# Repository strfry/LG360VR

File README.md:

# Summary

This about making the LG 360 VR Goggles usable with a normal DisplayPort outlet.

The LG360VR uses the "DisplayPort over USB-C" standard.
Our assumption is, that with little hardware effort, we can send a DisplayPort signal into it.

# Current State of things

- A passive PCB Adapter has been manufactured, though it doesn't work
- ~~Currently in the process of analyzing USB-PD communication, to figure out if this is the problem~~
  - Resolution: USB-PD Handshake is definitely necessary to get a display connection
- Now designing a new PCB with STM32F072 for PD Handshake and DisplayPort Redriver IC

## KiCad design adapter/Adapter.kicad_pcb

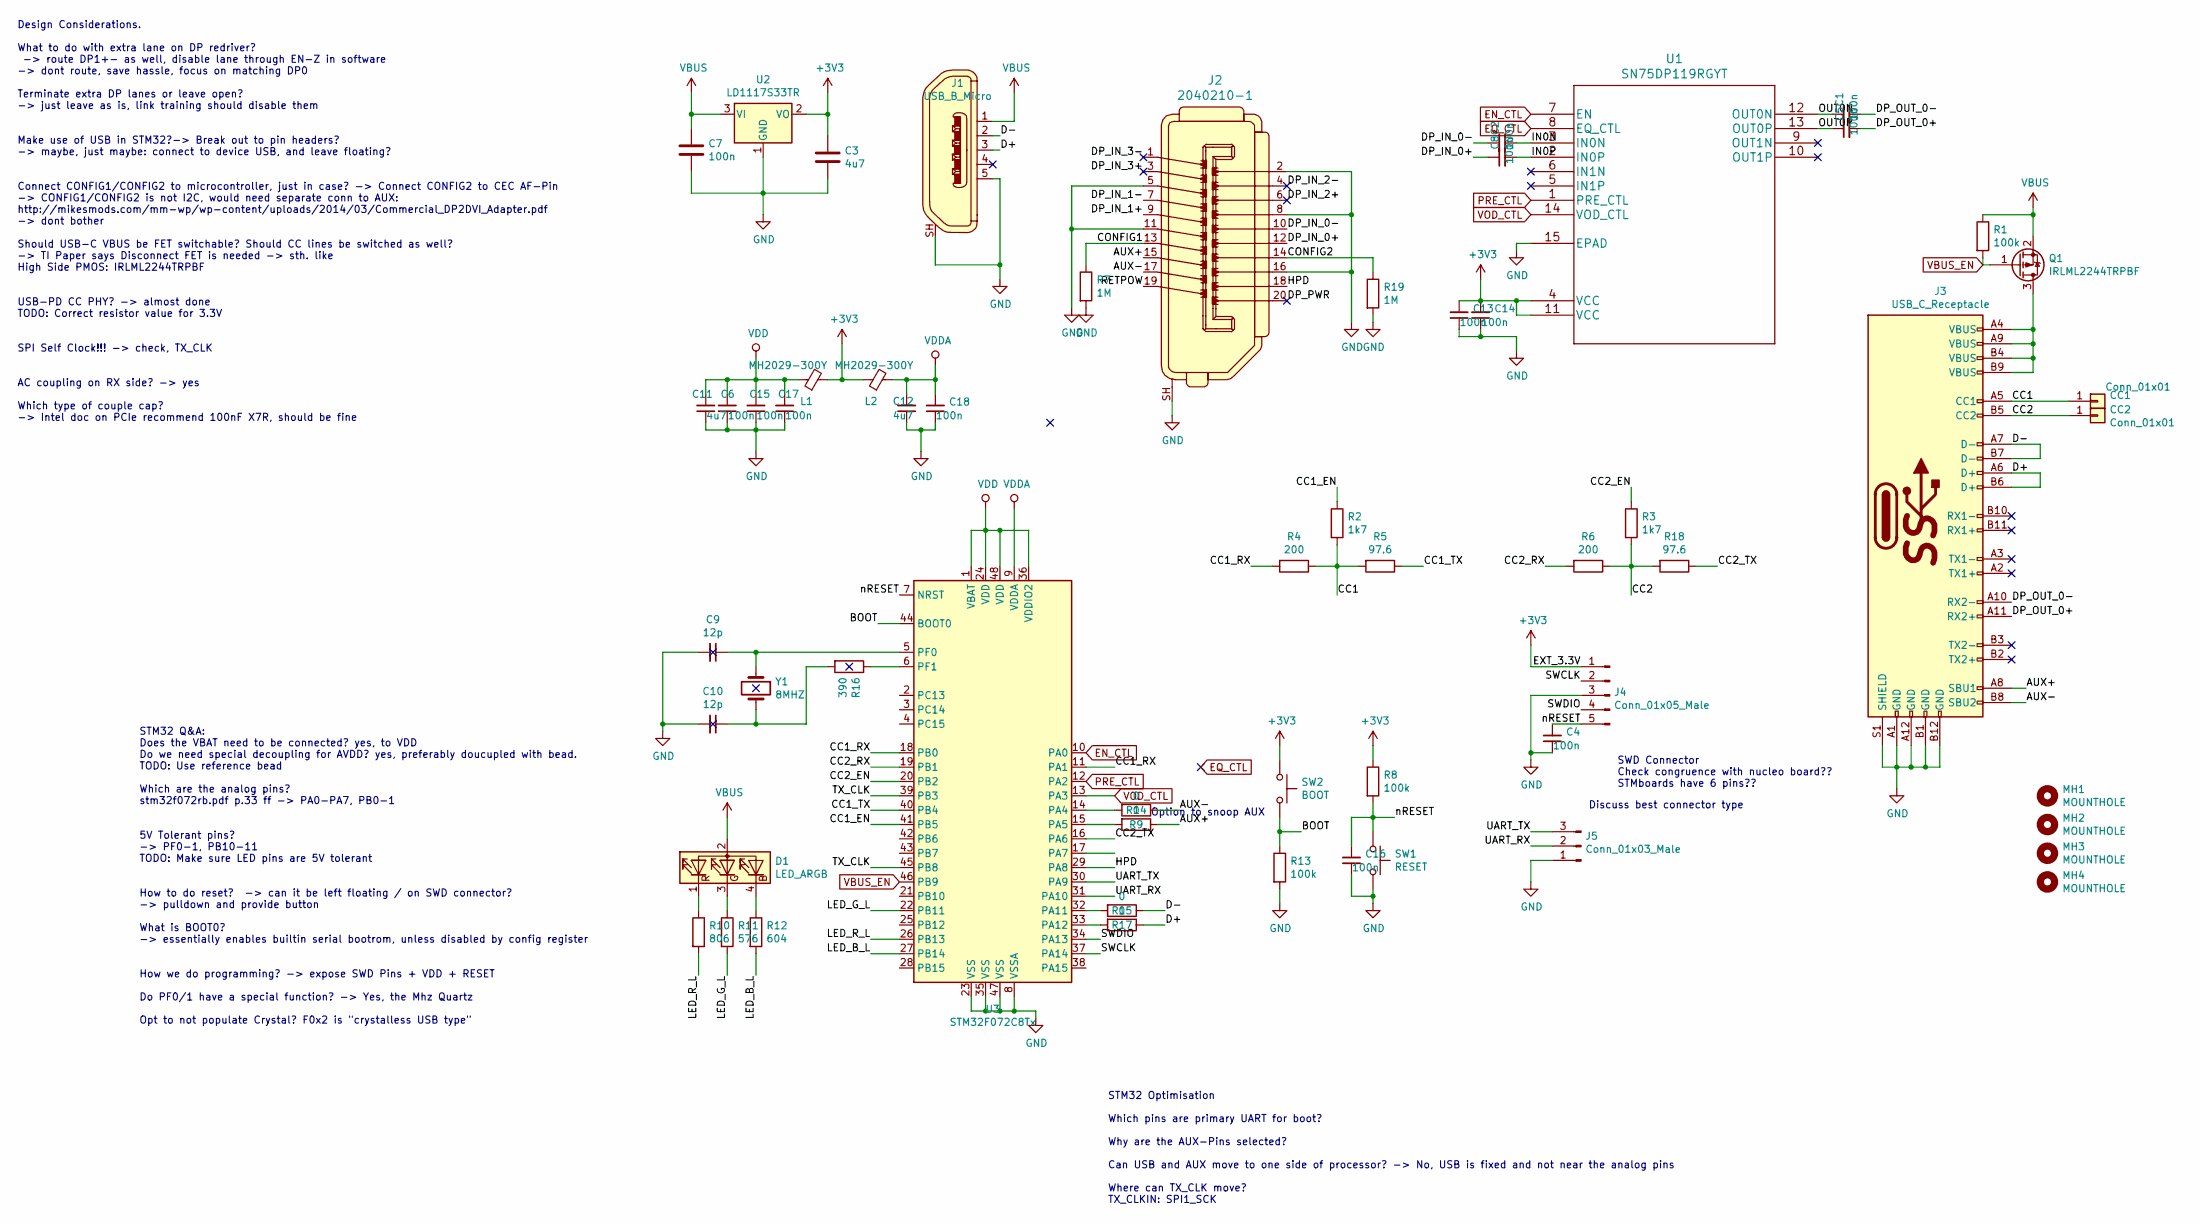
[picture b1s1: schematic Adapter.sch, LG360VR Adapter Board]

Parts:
C1, C2, C5, C8: 100n; C_0402_1005Metric
C3, C11, C12: 4u7; C_0603_1608Metric_Pad1.05x0.95mm_HandSolder
C4, C6, C7, C13, C14, C15, C16, C17, C18: 100n; C_0603_1608Metric_Pad1.05x0.95mm_HandSolder
C9, C10: 12p; C_0603_1608Metric_Pad1.05x0.95mm_HandSolder
CC1, CC2: Conn_01x01; TestPoint_Pad_D1.0mm
D1: LED_ARGB; LED_Cree-PLCC4_3.2x2.8mm_CCW
J1: USB_B_Micro; CONN-10118194-0001LF-FCI
J2: 2040210-1; DP1RD20JQ1R400
J3: USB_C_Receptacle; USB_C_Receptacle_Amphenol_12401610E4-2A
J4: Conn_01x05_Male; PinHeader_1x05_P2.54mm_Horizontal
J5: Conn_01x03_Male; PinHeader_1x03_P2.54mm_Horizontal
L1, L2: MH2029-300Y; L_0805_2012Metric_Pad1.15x1.40mm_HandSolder
MH1, MH2, MH3, MH4: MOUNTHOLE; MountingHole_2.5mm
Q1: IRLML2244TRPBF; SOT-23
R1, R8, R13: 100k; R_0603_1608Metric_Pad1.05x0.95mm_HandSolder
R2, R3: 1k7; R_0603_1608Metric_Pad1.05x0.95mm_HandSolder
R4, R6: 200; R_0603_1608Metric_Pad1.05x0.95mm_HandSolder
R5, R18: 97.6; R_0603_1608Metric_Pad1.05x0.95mm_HandSolder
R7, R19: 1M; R_0603_1608Metric_Pad1.05x0.95mm_HandSolder
R9, R14, R15, R17: 0; R_0603_1608Metric_Pad1.05x0.95mm_HandSolder
R10: 806; R_0603_1608Metric_Pad1.05x0.95mm_HandSolder
R11: 576; R_0603_1608Metric_Pad1.05x0.95mm_HandSolder
R12: 604; R_0603_1608Metric_Pad1.05x0.95mm_HandSolder
R16: 390; R_0603_1608Metric_Pad1.05x0.95mm_HandSolder
SW1: RESET; EVQPLMA15
SW2: BOOT; EVQPLMA15
U1: SN75DP119RGYT
U2: LD1117S33TR; SOT-223-3_TabPin2
U3: STM32F072C8Tx; LQFP-48_7x7mm_P0.5mm
Y1: 8MHZ; Crystal_SMD_TXC_7A-2Pin_5x3.2mm

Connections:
+3V3: C3.1, C13.2, C14.2, J4.1, L1.2, L2.1, R8.1, SW2.1, U1.4 (VCC), U1.11 (VCC), U2.2 (VO)
/AUX+: J2.15, J3.A8 (SBU1), R9.1
/AUX-: J2.17, J3.B8 (SBU2), R14.1
/BOOT: R13.1, SW2.2, U3.44 (BOOT0)
/CC1: CC1.1, J3.A5 (CC1), R2.2, R4.1, R5.2
/CC1_EN: R2.1, U3.41 (PB5)
/CC1_RX: R4.2, U3.11 (PA1), U3.18 (PB0)
/CC1_TX: R5.1, U3.40 (PB4)
/CC2: CC2.1, J3.B5 (CC2), R3.2, R6.1, R18.2
/CC2_EN: R3.1, U3.20 (PB2)
/CC2_RX: R6.2, U3.19 (PB1)
/CC2_TX: R18.1, U3.16 (PA6)
/CONFIG1: J2.13, R7.1
/CONFIG2: J2.14, R19.1
/D+: J1.3, J3.A6 (D+), J3.B6 (D+), R17.1
/D-: J1.2, J3.A7 (D-), J3.B7 (D-), R15.1
/DP_IN_0+: C8.1, J2.12
/DP_IN_0-: C2.1, J2.10
/DP_IN_1+: J2.9
/DP_IN_1-: J2.7
/DP_IN_2+: J2.6
/DP_IN_2-: J2.4
/DP_IN_3+: J2.3
/DP_IN_3-: J2.1
/DP_OUT_0+: C5.2, J3.A11 (RX2+)
/DP_OUT_0-: C1.2, J3.A10 (RX2-)
/DP_PWR: J2.20
/HPD: J2.18, U3.29 (PA8)
/IN0N: C2.2, U1.3 (IN0N)
/IN0P: C8.2, U1.2 (IN0P)
/LED_B_L: R12.2, U3.27 (PB14)
/LED_G_L: R11.2, U3.22 (PB11)
/LED_R_L: R10.2, U3.26 (PB13)
/OUT0N: C1.1, U1.12 (OUT0N)
/OUT0P: C5.1, U1.13 (OUT0P)
/RETPOW: J2.19
/SWCLK: J4.2, U3.37 (PA14)
/SWDIO: J4.4, U3.34 (PA13)
/TX_CLK: U3.39 (PB3), U3.45 (PB8)
/UART_RX: J5.2, U3.31 (PA10)
/UART_TX: J5.3, U3.30 (PA9)
/nRESET: C4.2, C16.2, J4.5, R8.2, SW1.1, U3.7 (NRST)
EN_CTL: U1.7 (EN), U3.10 (PA0)
EQ_CTL: U1.8 (EQ_CTL)
GND: C3.2, C4.1, C6.1, C7.2, C9.2, C10.2, C11.1, C12.1, C13.1, C14.1, C15.1, C16.1, C17.1, C18.1, J1.5, J1.SH, J2.2, J2.5, J2.8, J2.11, J2.16, J2.SH, J3.A1 (GND), J3.A12 (GND), J3.B1 (GND), J3.B12 (GND), J3.S1 (SHIELD), J4.3, J5.1, R7.2, R13.2, R19.2, SW1.2, U1.15 (EPAD), U2.1 (GND), U3.8 (VSSA), U3.23 (VSS), U3.35 (VSS), U3.47 (VSS)
unnamed: C9.1, U3.5 (PF0), Y1.1
unnamed: C10.1, R16.2, Y1.2
unnamed: D1.1 (RK), R10.1
unnamed: D1.3 (GK), R11.1
unnamed: D1.4 (BK), R12.1
unnamed: J3.A4 (VBUS), J3.A9 (VBUS), J3.B4 (VBUS), J3.B9 (VBUS), Q1.3 (D)
unnamed: R9.2, U3.15 (PA5)
unnamed: R14.2, U3.14 (PA4)
unnamed: R15.2, U3.32 (PA11)
unnamed: R16.1, U3.6 (PF1)
unnamed: R17.2, U3.33 (PA12)
PRE_CTL: U1.1 (PRE_CTL), U3.12 (PA2)
VBUS: C7.1, D1.2 (A), J1.1, Q1.2 (S), R1.1, U2.3 (VI)
VBUS_EN: Q1.1 (G), R1.2, U3.46 (PB9)
VDD: C6.2, C11.2, C15.2, C17.2, L1.1, U3.1 (VBAT), U3.24 (VDD), U3.36 (VDDIO2), U3.48 (VDD)
VDDA: C12.2, C18.2, L2.2, U3.9 (VDDA)
VOD_CTL: U1.14 (VOD_CTL), U3.13 (PA3)

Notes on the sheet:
STM32 Q&A: Does the VBAT need to be connected? yes, to VDD Do we need special decoupling for AVDD? yes, preferably doucupled with bead. TODO: Use reference bead Which are the analog pins? stm32f072rb.pdf p.33 ff -> PA0-PA7, PB0-1 5V Tolerant pins? -> PF0-1, PB10-11 TODO: Make sure LED pins are 5V t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
Design Considerations. What to do with extra lane on DP redriver? -> route DP1+- as well, disable lane through EN-Z in software -> dont route, save hassle, focus on matching DP0 Terminate extra DP lanes or leave open? -> just leave as is, link training should disable them Make use of USB in STM32?-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
SWD Connector Check congruence with nucleo board?? STMboards have 6 pins??
Discuss best connector type
Option to snoop AUX
STM32 Optimisation Which pins are primary UART for boot? Why are the AUX-Pins selected? Can USB and AUX move to one side of processor? -> No, USB is fixed and not near the analog pins Where can TX_CLK move? TX_CLKIN: SPI1_SCK

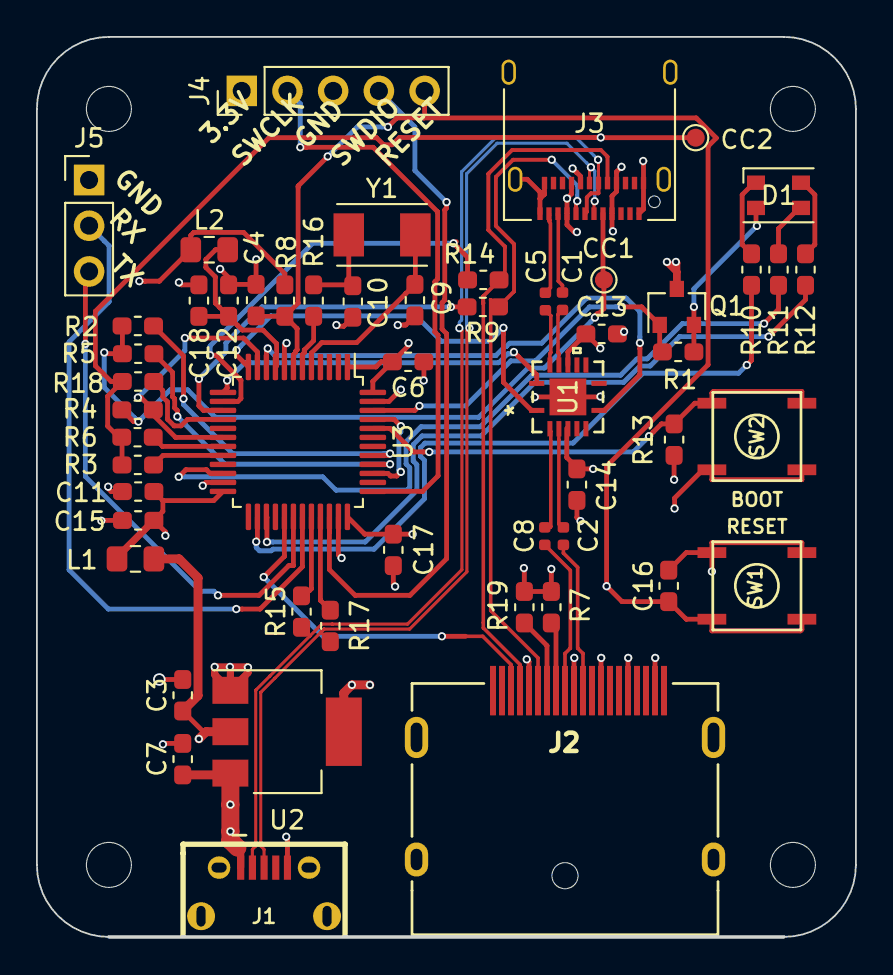
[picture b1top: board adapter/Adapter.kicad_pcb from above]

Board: 4 copper layers, 45.4 x 49.9 mm, 58 parts (0 on the bottom side), 53 nets.

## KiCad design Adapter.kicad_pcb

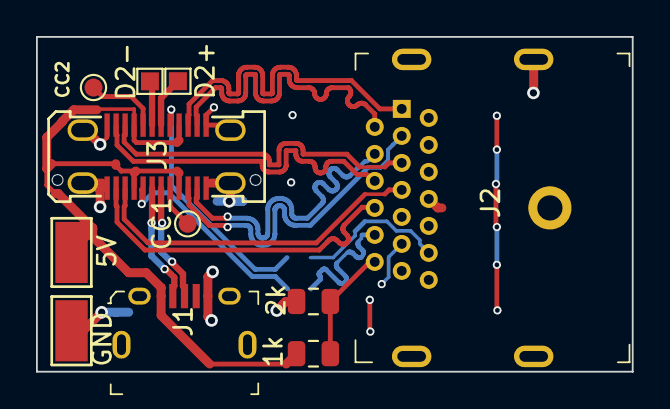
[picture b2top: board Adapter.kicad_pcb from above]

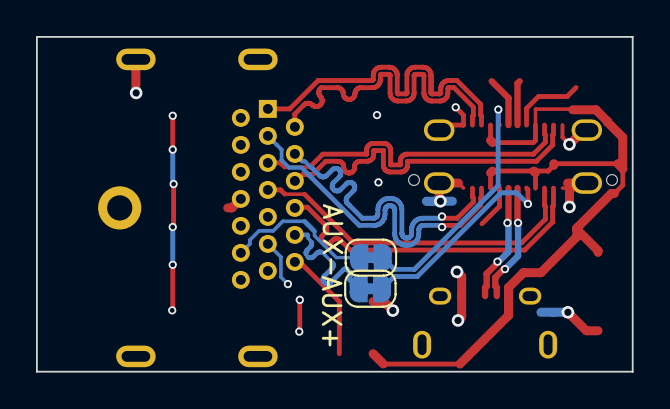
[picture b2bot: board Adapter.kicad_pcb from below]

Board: 4 copper layers, 33.1 x 18.6 mm, 13 parts (2 on the bottom side), 21 nets.

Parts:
1k: 1k; R_0805_2012Metric
2k: 2k; R_0805_2012Metric
5V: Conn_01x01; TestPoint_Keystone_5015_Micro-Minature
AUX+: Jumper; SolderJumper-2_P1.3mm_Bridged_RoundedPad1.0x1.5mm
AUX-: Jumper; SolderJumper-2_P1.3mm_Bridged_RoundedPad1.0x1.5mm
CC1, CC2: Conn_01x01; TestPoint_Pad_D1.0mm
D2+, D2-: Conn_01x01; TestPoint_Pad_1.0x1.0mm
GND: Conn_01x01; TestPoint_Keystone_5015_Micro-Minature
J1: USB_B_Micro; USB_Micro_B_Female_10118194-0001LF
J2: 2040210-1; DisplayPort_2040210-1
J3: USB_C_Receptacle; DX07S024WJ3R400

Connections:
/AUX+: AUX+.2, J2.15
/AUX-: AUX-.2, J2.17
/CC1: CC1.1, J3.A5
/CC2: CC2.1, J3.B5
/D2+: D2-.1, J3.B6
/D2-: D2+.1, J3.B7
/D+: J1.3, J3.A6
/D-: J1.2, J3.A7
/DP0+: J2.12, J3.A11
/DP0-: J2.10, J3.A10
/DP1+: J2.9, J3.B2
/DP1-: J2.7, J3.B3
/DP2+: J2.6, J3.A2
/DP2-: J2.4, J3.A3
/DP3+: J2.3, J3.B11
/DP3-: J2.1, J3.B10
/HPD: 1k.2, 2k.1, J2.18
/pAUX+: AUX+.1, J3.A8
/pAUX-: AUX-.1, J3.B8
GND: 2k.2, GND.1, J1.5, J2.2, J2.5, J2.8, J2.11, J2.16, J2.SH, J3.A1, J3.A12, J3.B1, J3.B12, J3.S1
VBUS: 1k.1, 5V.1, J1.1, J3.A4, J3.A9, J3.B4, J3.B9

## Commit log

2018-07-08 initial version (with most likely wrong lane ordering)
2018-07-08 Add digikey library as submodule
2018-07-09 Reverse DP Lanes, connect Shield to GND
2018-07-09 New design with DP and USB-mB on same side
2018-07-21 4-Layer-Design with correct DP Lane polarity and impedance matching
2018-07-21 cosmetic changes
2018-07-22 Re-matched and DRCed for OSHPark's 4 Layer Process
2018-10-21 Move PCB stuff into hardware/ directory
2018-10-21 rename hardware to adapter, add USB-C footprint
2018-10-28 Dumping README and firmware, without proper build system...
2018-12-18 Link EC firmware as submodule
2019-01-28 created new footprint and symbols for DP redriver IC
2019-01-29 Design considerations and fixed most external circuitry for STM32
2019-02-01 cleared a bunch of questions
2019-02-01 used most of stm32 pinning from twinkie board
2019-02-03 pre-place most of components
2019-02-03 Added 3D STEP for micro-USB Jack
2019-02-03 Compatible Molex DisplayPort connector 3d file
2019-02-03 Step file for MicroUSB
2019-02-03 sync changs from tmp checkout
2019-02-03 renamed custom footprints
2019-02-04 more 3d packages...
2019-02-04 remove the bead for the DP119
2019-02-04 Added 2 missing STEP files
2019-02-06 state published at http://strfry.org/lg360vr-schematic.pdf
2019-02-08 Replaced SN75DP119 symbol/footprint with premade one from Arrow librarian
2019-02-08 cleared all order number for Arrow
2019-02-13 placement mostly done
2019-02-14 first fully routed
2019-02-16 shifting back some components from the USB-C jack
2019-02-20 Connect EXT3.3V to 3.3V
2019-02-20 squashed out a mm to stay within 50x50 mm discount
2019-02-20 retraced impedance critical paths
2019-02-20 corrected USB impedance
2019-02-20 remove silkscreen from pin header footprints
2019-02-20 no silkscreen at bottom
2019-03-03 link to new firmware
2019-03-31 simple enclosure
2019-04-02 logo and optimized holes
2019-04-23 add stl exports
2019-05-01 correctly re-exported upper_case (with USB-C hole)
2019-06-09 fix distance between DP and µUSB connector
2019-06-09 fix the PA1 connection (the cheap way, as in prototype)
2019-06-09 enter unpopulated parts note

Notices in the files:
parts and their libraries:
Copyright 2016 Accelerated Designs. All rights reserved.
